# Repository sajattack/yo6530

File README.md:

## Dependencies
- FPGA Toolchain: https://github.com/YosysHQ/oss-cad-suite-build
- Simulator: https://verilator.org/guide/latest/install.html
- C++ toolchain: gcc and gnu make
- Trace Viewer: https://gtkwave.sourceforge.net/
- SPI flash programmer: https://www.flashrom.org/
- Linter: https://github.com/chipsalliance/verible
- Hardware research in dwfpy directory uses a Digilent Digital Discovery, python and the dwfpy library to probe and stimulate a MOS6532, for understanding expected behaviour from real hardware

## Target Hardware
https://github.com/daglem/redip-riot

## Programming the board using Raspberry Pi (3B) with flashrom
### Wiring

| Raspi pin name/num  | ReDIP RIOT name/num|
| ------------------- | -----------------|
| SCK / 23            | SPI_SCLK / 3     |
| MISO / 21           | SPI_SIO1 / 5     |
| MOSI / 19           | SPI_SIO0 / 7     |
| CE0 / 24            | SPI_CS / 1       |
| GPIO25 / 22         | CDONE / 2        |
| 3v3 / 17            | 3v3 / 8          |
| GND / 20            | GND / 6          |
| GPIO24 / 18         | CRESET / 4       |

```sh
make MCS6530_002=1 # build the project
scp build/mcs6530.bin pi@<your-pi's-ip>: # copy the build artifact to the pi for flashing
ssh pi@<your-pi's-ip> # connect to the pi
sudo raspi-config # go into the interfaces menu and enable spi after running this command
pinctrl set 24 op dl # put the board into programming mode by setting creset low
flashrom -p linux_spi:dev=/dev/spidev0.0,spispeed=20000 # if this detects the device, all is good, otherwise check your spi is enabled and your wiring
truncate -s 128K mcs6530.bin # pad the rom to 128K
flashrom -p linux_spi:dev=/dev/spidev0.0,spispeed=20000 -w mcs6530.bin # write the flash
pinctrl set 24 ip pu # exit programming mode by returning creset to input pullup
```

## Building and running the simulation tests
```sh
make MCS6530_002=1 sim
./obj_dir/Vverilator_top # this will throw assertion errors if the tests fail
```
Also you can examine the logic signals output during the test in the Vverilator_top.vcd file using [GTKWave](https://gtkwave.sourceforge.net/)

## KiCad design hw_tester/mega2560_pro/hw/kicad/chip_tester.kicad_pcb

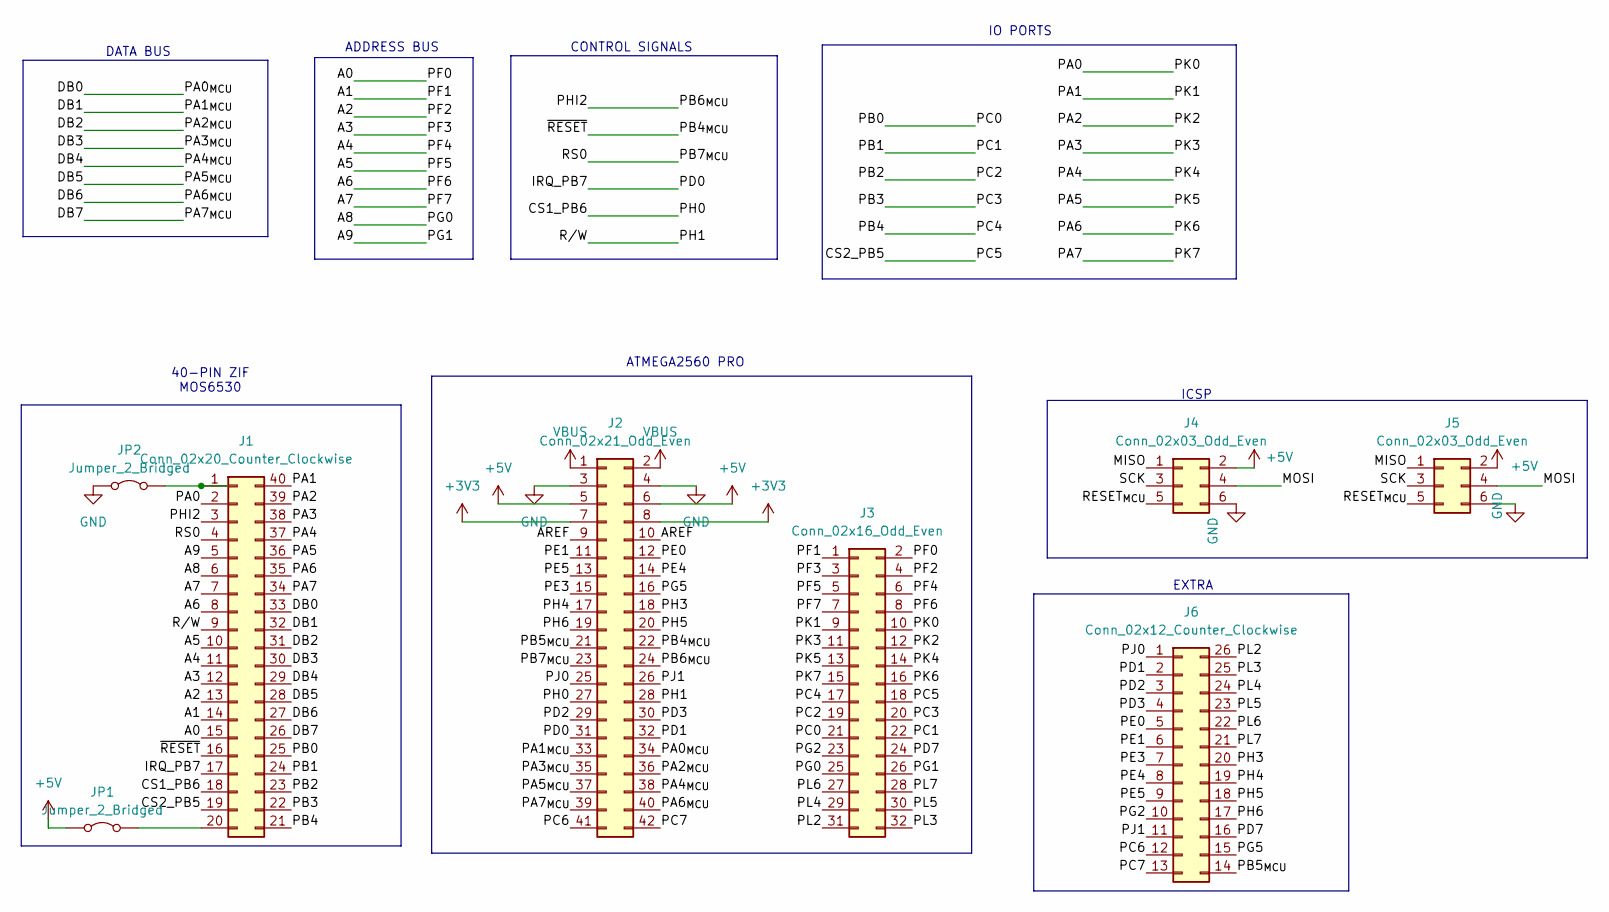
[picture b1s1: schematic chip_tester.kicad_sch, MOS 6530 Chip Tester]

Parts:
J1: Conn_02x20_Counter_Clockwise; 3M_Textool_240-1288-00-0602J_2x20_P2.54mm
J2: Conn_02x21_Odd_Even; PinHeader_2x21_P2.54mm_Vertical
J3: Conn_02x16_Odd_Even; PinHeader_2x16_P2.54mm_Vertical
J4, J5: Conn_02x03_Odd_Even; PinHeader_2x03_P2.54mm_Vertical
J6: Conn_02x12_Counter_Clockwise; PinHeader_2x13_P2.54mm_Vertical
JP1, JP2: Jumper_2_Bridged; SolderJumper-2_P1.3mm_Bridged_RoundedPad1.0x1.5mm

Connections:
+3V3: J2.7, J2.8
+5V: J2.5, J2.6, J4.2, J5.2, JP1.1 (A)
/A0: J1.15, J3.2
/A1: J1.14, J3.1
/A2: J1.13, J3.4
/A3: J1.12, J3.3
/A4: J1.11, J3.6
/A5: J1.10, J3.5
/A6: J1.8, J3.8
/A7: J1.7, J3.7
/A8: J1.6, J3.25
/A9: J1.5, J3.26
/AREF: J2.9, J2.10
/CS1_PB6: J1.18, J2.27
/CS2_PB5: J1.19, J3.18
/DB0: J1.33, J2.34
/DB1: J1.32, J2.33
/DB2: J1.31, J2.36
/DB3: J1.30, J2.35
/DB4: J1.29, J2.38
/DB5: J1.28, J2.37
/DB6: J1.27, J2.40
/DB7: J1.26, J2.39
/IRQ_PB7: J1.17, J2.31
/MISO: J4.1, J5.1
/MOSI: J4.4, J5.4
/PA0: J1.2, J3.10
/PA1: J1.40, J3.9
/PA2: J1.39, J3.12
/PA3: J1.38, J3.11
/PA4: J1.37, J3.14
/PA5: J1.36, J3.13
/PA6: J1.35, J3.16
/PA7: J1.34, J3.15
/PB0: J1.25, J3.21
/PB1: J1.24, J3.22
/PB2: J1.23, J3.19
/PB3: J1.22, J3.20
/PB4: J1.21, J3.17
/PB4_{MCU}: J1.16, J2.22
/PB5_{MCU}: J2.21, J6.14
/PB6_{MCU}: J1.3, J2.24
/PB7_{MCU}: J1.4, J2.23
/PC6: J2.41, J6.12
/PC7: J2.42, J6.13
/PD1: J2.32, J6.2
/PD2: J2.29, J6.3
/PD3: J2.30, J6.4
/PD7: J3.24, J6.16
/PE0: J2.12, J6.5
/PE1: J2.11, J6.6
/PE3: J2.15, J6.7
/PE4: J2.14, J6.8
/PE5: J2.13, J6.9
/PG2: J3.23, J6.10
/PG5: J2.16, J6.15
/PH1: J1.9, J2.28
/PH3: J2.18, J6.20
/PH4: J2.17, J6.19
/PH5: J2.20, J6.18
/PH6: J2.19, J6.17
/PJ0: J2.25, J6.1
/PJ1: J2.26, J6.11
/PL2: J3.31, J6.26
/PL3: J3.32, J6.25
/PL4: J3.29, J6.24
/PL5: J3.30, J6.23
/PL6: J3.27, J6.22
/PL7: J3.28, J6.21
/RESET_{MCU}: J4.5, J5.5
/SCK: J4.3, J5.3
GND: J2.3, J2.4, J4.6, J5.6, JP2.1 (A)
unnamed: J1.1, JP2.2 (B)
unnamed: J1.20, JP1.2 (B)
VBUS: J2.1, J2.2

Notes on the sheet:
ADDRESS BUS
IO PORTS
ICSP
40-PIN ZIF MOS6530
EXTRA
ATMEGA2560 PRO
DATA BUS
CONTROL SIGNALS

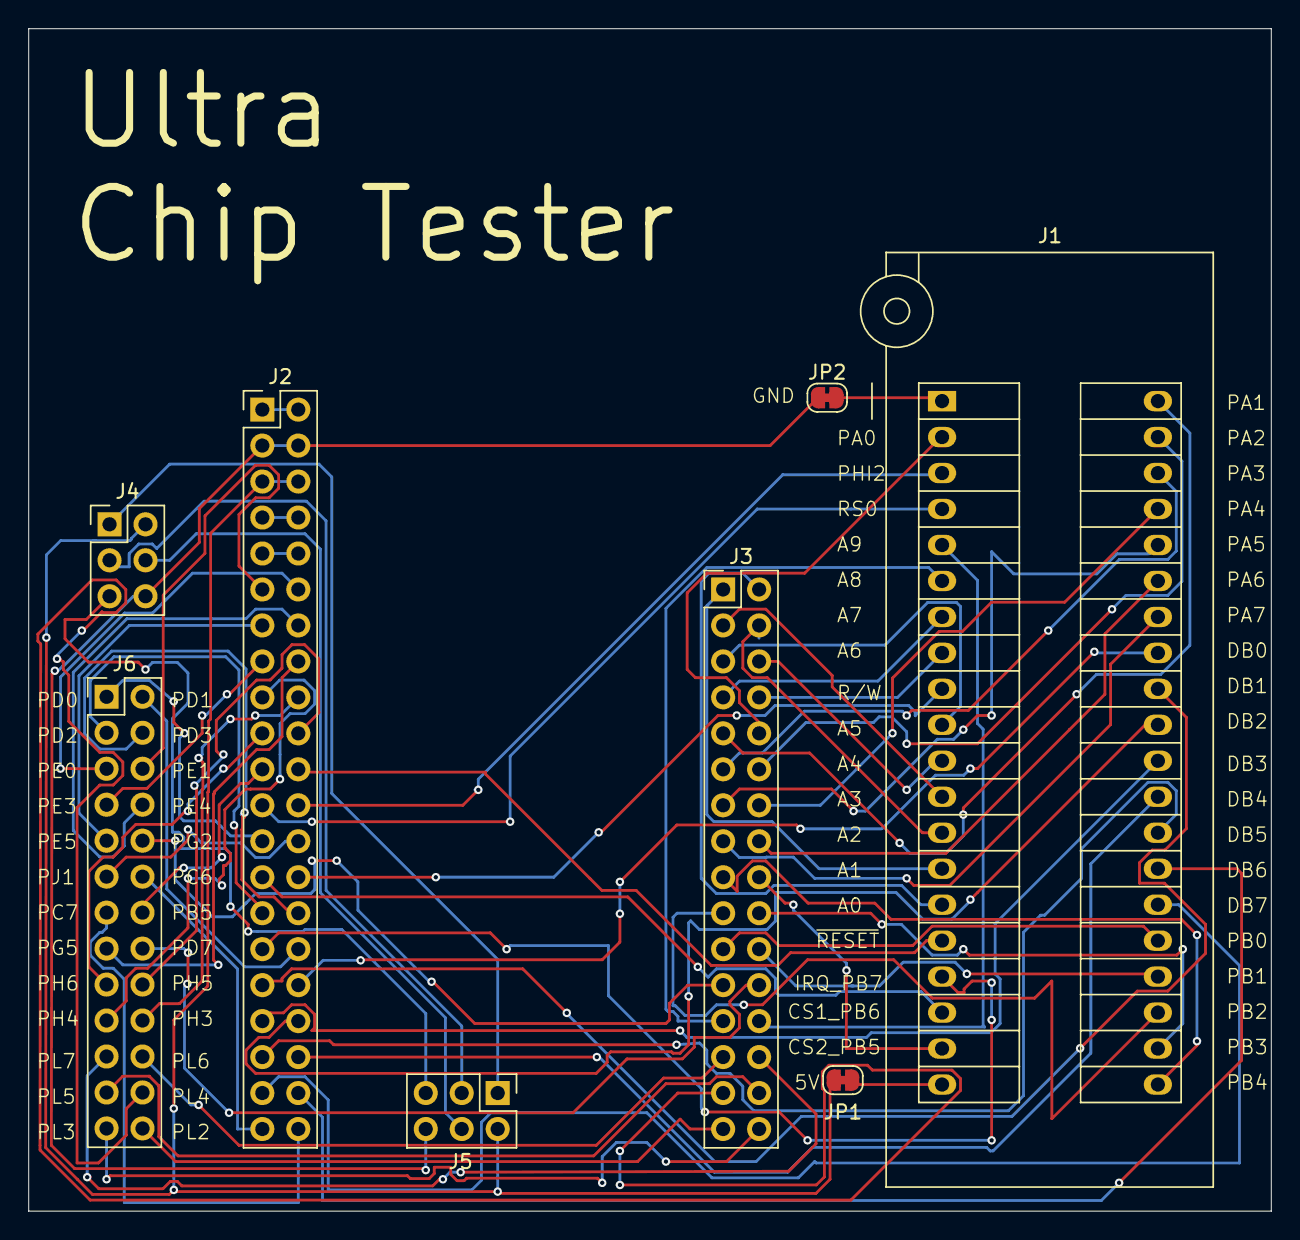
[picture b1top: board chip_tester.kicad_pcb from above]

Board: 2 copper layers, 87.8 x 83.5 mm, 8 parts (0 on the bottom side), 75 nets.

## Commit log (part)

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2023-11-13 timer test rom, new pcf, top file, makefile tweaks
2023-11-13 put the DDRs back where they belong
2023-11-27 Update reference code license per email
    "A Berkeley license is fine. Note that the whole project includes a 6502 core that's not under my license."
2023-11-27 fix name typo in license
2023-12-13 some fixes
2023-12-13 fix memory inferring as logic, probably break cycle timing
2023-12-18 verilator
2023-12-18 rom verilator output seems more sane
2023-12-20 test skeleton
2024-01-10 ram test
2024-01-17 IO test
2024-01-17 timer test & fix some address decoding bugs
2024-01-17 rs0 fixup
2024-01-21 fix warnings and formatting
2024-01-22 start working on cycle timing accuracy
    NOTE: once the clock cycles were reduced the timer code started
    failing assertions. TODO.
2024-01-22 make simulation timing more harsh/accurate
2024-01-24 fix the timer
2024-01-31 refactor into more modules
2024-02-11 fix timer sim
2024-02-14 disable timer_irq until I understand it better
2024-05-22 wip irq stuff
2024-06-12 more fiddling with irq
2024-06-12 re-enable wall
2024-07-17 add hardware irq timing experiment using Digilent Digital Discovery
2024-08-04 irq timing experiment that properly detects edge triggers
2024-08-05 switch to 6530-002
2024-08-05 cleanup irq research a bit
2024-08-05 add some notes and fix some mistakes (maybe?)
2024-08-05 additional note
2024-08-05 I'm not sure if rs0 is active low or active high
2024-08-06 disable io and timer
2024-08-06 set rom to 003
2024-08-06 rom testing on hw, make draw, makefile cleanup, format, io type tweaks and more!
2024-08-07 bring over some useful stuff from the rr branch
2024-08-12 fix address decoding and multi-function pins
2024-08-21 new pcf, reorg of hw_tests, misc other changes
2024-08-21 bus read/write functions for testing
2024-08-21 rom tests (still needs a better panic handler)
2024-08-26 semifunctional rom tester
2024-09-01 chip tester pcb
2024-09-01 minor board layout changes
2024-09-11 remap pins
2024-09-12 ROM 003 hwtest passing
2024-09-13 ch-ch-ch-changes
2024-09-13 minor timer changes
2024-09-13 RAM works
2024-09-13 fix timer validation
2024-09-18 some random stuff I didn't commit before
2024-09-21 hardware test suite fully passes
2024-09-21 hw tester fixup
2024-09-22 minor changes
2024-09-25 change addresses to hex
2024-10-01 io is broken trying to fix
2024-10-03 io fixes?
2024-10-05 switch pintype and use negedge of clock, also change timer tests
2024-10-10 trying to add a spi flash programmer to the tester
2024-10-11 fiddling with timing
2024-10-13 make tester more slightly more agressive with timing
2024-10-14 run sim with 2x clock
2024-10-15 fix some dumb bugs
2025-01-27 image of kim-1 running off redip-rriot/yo6530
2025-01-30 sourcehut ci
2025-01-30 add build badge to readme
2025-01-30 build both variants currently supported
2025-02-07 use roms with 00 filler bytes (Fixes issue #2)
2025-02-12 broken parameter code
2025-02-26 couldn't figure out how not to have a default for a parameter, whatever
2025-05-02 fix timer issue with Asteroid game (Fixes #3)
2025-05-12 more timer fixes
2025-06-06 fiddling with timer and io, trying to get tape input (loading) working
2025-06-10 debug enhancements: writable rom and preloaded NMI/BREAK vectors
2025-06-11 fixes to debug functionality
